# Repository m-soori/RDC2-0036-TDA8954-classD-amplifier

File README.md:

<p></p>

<p>Модуль RDC2-0036 представляет собой высокопроизводительный усилитель мощности класса D. УНЧ построен на микросхеме TDA8954. Это стереофонический аналоговый чип с цифровым усилителем, предназначенный для работы с 4-омными громкоговорителями мощностью до 210 Вт на канал.RDC2-0036 характеризуется очень низким уровнем шума и низким током покоя.<br>На аналоговый вход усилителя можно подавать как несимметричный так и симметричный (дифференциальный) сигнал.<br> Встроенная система защиты отслеживает: перегрев, перегрузку и короткое замыкание выходов. При наличии одной из вышеперечисленных ошибок усилитель отключается, а после устранения ошибки восстанавливает работу.<br>Для обеспечения высококачественного высокоэффективного усиления звука требуется простой пассивный фильтр демодуляции цифрового сигнала это модуль LCF1. Для управления режимами усилителя необходим дополнительный источник напряжения - 5В. Это напряжение можно получить с помощью модуля RDC1-0013 5V. Для подключения этого модуля на плате установлен разъём (XP5).</p>
<h2>Технические характеристики</h2>
<p>Напряжение питания выходного каскада: двухполярное от ±12.5В до ±37В<br>Количество каналов: 2 x SE, 1 x BTL<br>Сопротивление нагрузки SE: 4-8 Ом<br>Сопротивление нагрузки BTL: 8 Ом<br>Выходная мощность SE: 210 Вт / 4 Ом<br>Выходная мощность BTL: 420 Вт / 8 Ом <br>Коэффициент нелинейных искажений:0.05%<br>КПД с нагрузкой 6Ом: 90%</p>
<p>Схема усилителя с выходными фильтрами и дополнительным источником напряжения - 5В.</p>
<p></p>
<p>Блок-схема усилителя с выходными фильтрами.</p>
<p></p>
<p>Подробную инструкцию по включению и конфигурации усилителя можно найти в разделе «Документы».</p>
<p>Это открытый проект! Лицензия, под которой он распространяется – <a href="https://creativecommons.org/licenses/by-sa/3.0/">Creative Commons - Attribution - Share Alike license</a>.</p>

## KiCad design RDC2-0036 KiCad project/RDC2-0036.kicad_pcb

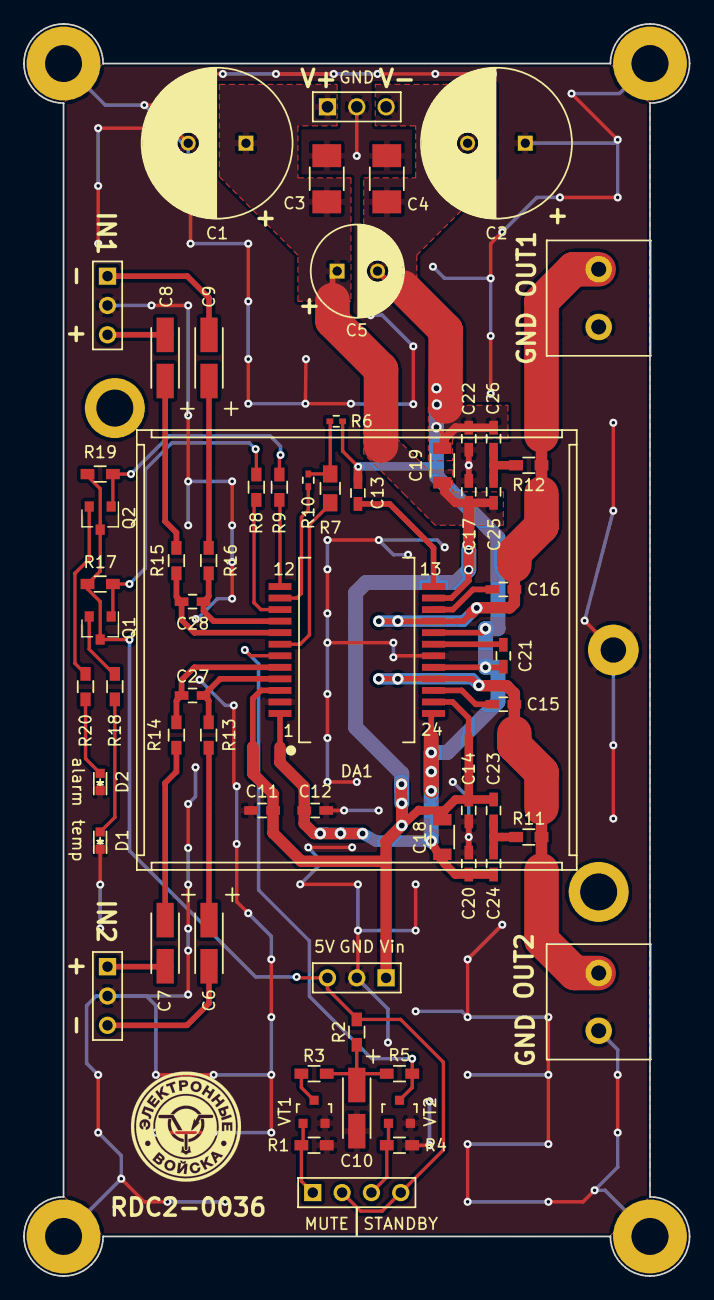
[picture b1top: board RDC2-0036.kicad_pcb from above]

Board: 2 copper layers, 57.7 x 108.5 mm, 63 parts (0 on the bottom side), 40 nets.

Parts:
C1, C2: CP; C_Radial_D13_L21_P5
C3, C4: C; C_1210_HandSoldering
C5: CP; C_Radial_D8_L11.5_P3.5
C6, C7, C8, C9, C10: CP; TantalC_SizeA_EIA-3216_HandSoldering_mm
C11, C12, C13, C14, C15, C16, C17, C20, C21, C22, C23, C24, C25, C26, C27, C28: C; C_0603_HandSoldering
C18, C19: C; C_1206
D1, D2: LED; LED_0603
DA1: TDA8954; HSOP24
HeatSink: Heatsink_37x37mm_SpringFixation
Q1, Q2: BC858; SOT-23
R1, R2, R3, R4, R5, R8, R9, R11, R12: R; R_0603_HandSoldering
R6, R10: R; C_0402
R7: R; C_0805_HandSoldering
R13, R14, R15, R16: 5K6; R_0603_HandSoldering
R17, R19: 10K; R_0603_HandSoldering
R18, R20: 1K; R_0603_HandSoldering
VT1, VT2: BSS138; SOT-23_mm
XP1, XP2, XP4, XP5: CONN_01X03; Pin_Header_Straight_1x03_mm
XP3: CONN_01X04; Pin_Header_Straight_1x04_mm
XS1, XS2: CONN_01X02; Clem_2Pos_P5

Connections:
5V: Q1.3, Q2.3, R2.2, R17.1, R19.1, XP3.2, XP3.4, XP5.3
ALARM: Q2.1, R9.1, R19.2
GND: C1.2, C2.1, C3.2, C4.1, C10.2, C11.2, C12.2, C14.2, C17.2, C20.2, C22.2, D1.1, D2.1, DA1.2, DA1.19, R1.2, R4.2, VT1.2, VT2.2, XP1.2, XP2.2, XP4.2, XP5.2, XS1.2, XS2.2
Mute: R1.1, VT1.1, XP3.1
unnamed: C6.1, R13.1
unnamed: C6.2, XP1.3
unnamed: C7.1, R14.1
unnamed: C7.2, XP1.1
unnamed: C8.1, R15.1
unnamed: C8.2, XP2.3
unnamed: C9.1, R16.1
unnamed: C9.2, XP2.1
unnamed: C10.1, R2.1, R3.1, R5.2
unnamed: C13.1, DA1.13
unnamed: C15.2, DA1.22
unnamed: C16.2, DA1.15
unnamed: C21.1, DA1.18
unnamed: C23.1, C24.1, R11.2
unnamed: C25.1, C26.1, R12.2
unnamed: C27.1, DA1.4, R13.2
unnamed: C27.2, DA1.5, R14.2
unnamed: C28.1, DA1.8, R15.2
unnamed: C28.2, DA1.9, R16.2
unnamed: D1.2, R18.2
unnamed: D2.2, R20.2
unnamed: DA1.6, R5.1, VT2.3
unnamed: DA1.7, R7.2
unnamed: DA1.10, R8.2
unnamed: DA1.11, R10.2
unnamed: DA1.12, R9.2
unnamed: Q1.2, R18.1
unnamed: Q2.2, R20.1
unnamed: R3.2, VT1.3
OSCREF: R6.2, R7.1, R10.1
OUT1: C16.1, DA1.16, R12.1, XS2.1
OUT2: C15.1, DA1.21, R11.1, XS1.1
Standby: R4.1, VT2.1, XP3.3
TEMP: Q1.1, R8.1, R17.2
VA+: C1.1, C3.1, C5.1, C11.1, C14.1, C17.1, C18.1, C19.1, C23.2, C25.2, DA1.3, DA1.14, DA1.23, XP4.1, XP5.1
VA-: C2.2, C4.2, C5.2, C12.1, C13.2, C18.2, C19.2, C20.1, C21.2, C22.1, C24.2, C26.2, DA1.1, DA1.17, DA1.20, DA1.24, R6.1, XP4.3

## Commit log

2018-09-27 KiCad project
2018-09-27 Gerber files
